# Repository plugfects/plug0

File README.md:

plug0
=====

Open source compact effects unit for eletric guitar

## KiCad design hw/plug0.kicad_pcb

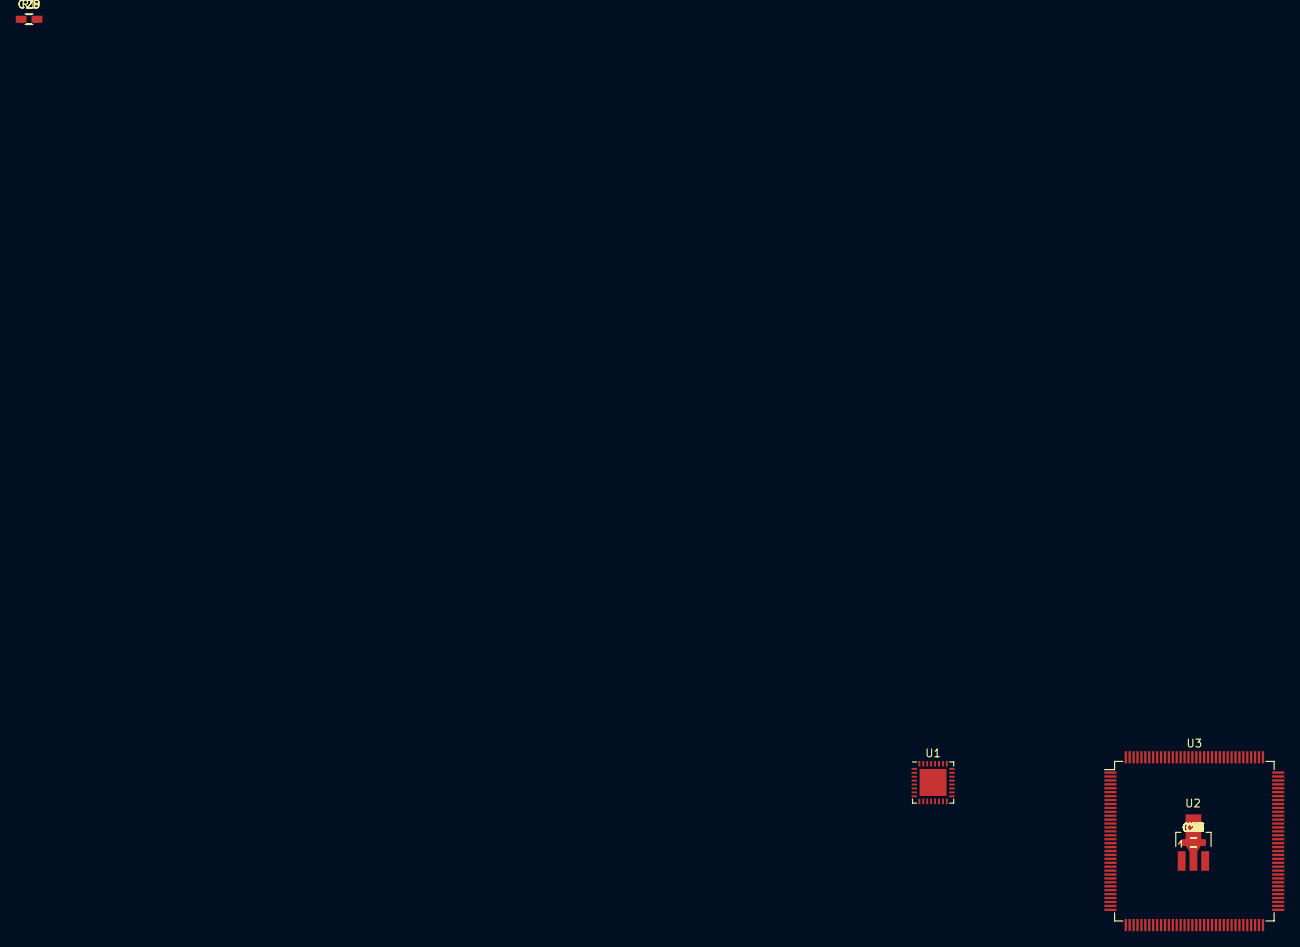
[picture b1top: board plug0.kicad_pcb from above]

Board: 2 copper layers, 33 parts (0 on the bottom side), 10 nets, no tracks yet.

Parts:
C1, C2, C3, C4, C5, C6, C9, C12: 10uF; C_0603
C7, C8: 47uF; C_0603
C10: 100n; C_0603_HandSoldering
C11: 10u; C_0603_HandSoldering
C13, C14, C15, C16, C17, C18, C19, C20, C21, C22, C23, C24, C25: 100nF; C_0603
C26, C27: 22nF; C_0603
C28, C29: 2.2uF; C_0603
R1: 10K; R_0603_HandSoldering
U1: pcm3070i; QFN-32-1EP_5x5mm_Pitch0.5mm
U2: AZ1117C; SOT89-3_Housing_Handsoldering
U3: stm32fxxxz; LQFP-144_20x20mm_Pitch0.5mm

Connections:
GND: C1.2, C2.2, C3.2, C4.2, C5.2, C6.2, C9.2, C10.2, C11.2, C12.2, C13.2, C14.2, C15.2, C16.2, C17.2, C18.2, C19.2, C20.2, C21.2, C22.2, C23.2, C24.2, C26.2, C27.2, C28.2, C29.2, U2.1, U3.16, U3.31, U3.38, U3.51, U3.61, U3.83, U3.94, U3.107, U3.120, U3.130
unnamed: C7.2, U1.27
unnamed: C8.2, U1.25
unnamed: C26.1, U3.24
unnamed: C27.1, U3.23
unnamed: C28.1, U3.71
unnamed: C29.1, U3.106
VAA: C25.1, U3.32, U3.33
VCC: C10.1, U2.3
VDD: C1.1, C2.1, C3.1, C4.1, C5.1, C6.1, C9.1, C11.1, C12.1, C13.1, C14.1, C15.1, C16.1, C17.1, C18.1, C19.1, C20.1, C21.1, C22.1, C23.1, C24.1, U1.18, U1.24, U1.29, U1.30, U2.2, U3.6, U3.17, U3.30, U3.39, U3.52, U3.62, U3.72, U3.84, U3.95, U3.108, U3.121, U3.131, U3.143, U3.144

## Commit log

2015-10-05 Updated audio circuit to be modular
2016-02-23 add waffle.io badge
2016-02-24 Iniciada a documentação com sphinx
2016-03-16 Primeira versão do diagrama de blocos. Close #10
2016-03-21 Imagens do sistema criadas
2016-03-21 Corrigidos os caminhos no projeto do kicad
2016-03-25 XFor my EE Senior Design project I'm designing an Audio DSP platform with external memory. I've opted to go for SDRAM for cost and size reasons. Got the boards made and apart from a few glitches thin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
2016-03-27 Created kicad_pcb, added STMCube project, added netlist, Added audio plug
2016-03-29 STMCube project update with SAI configuration
2016-03-30 Reorganizada a folha mestre, ajustes nos PN e criação de folha hierárquica para gestão de bateria e alimentação
